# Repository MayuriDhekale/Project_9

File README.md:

# Project_9
<br>
<h2>A minimal RP2040 board designed in KiCad</h2>
<br>
I designed a small RP2040 board (like a Raspberry Pi Pico) in KiCad. I followed Raspberry Pi's official design guide to learn how a real board is made.

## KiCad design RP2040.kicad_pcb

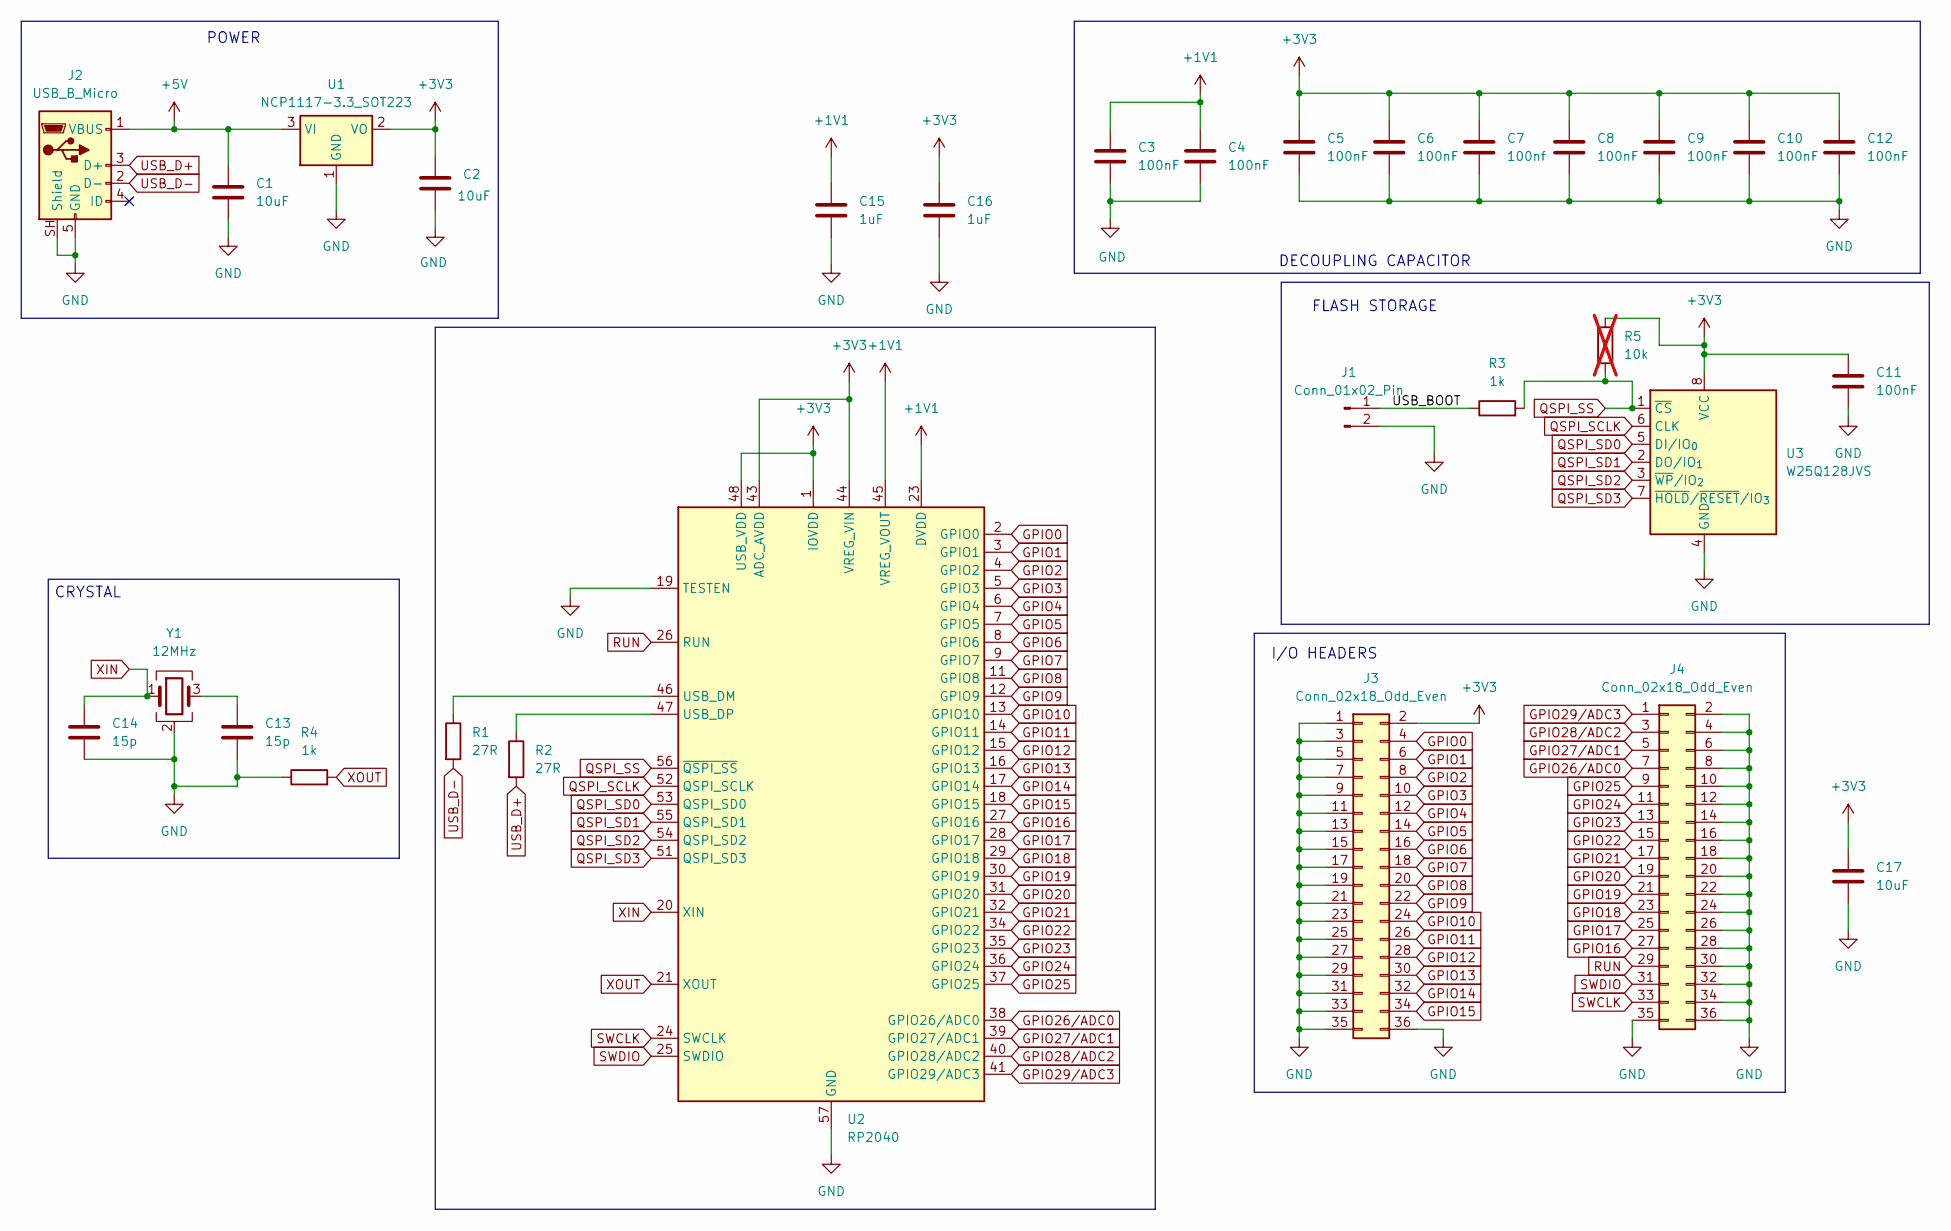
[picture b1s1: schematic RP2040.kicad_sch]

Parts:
C1, C2, C17: 10uF; C_0603_1608Metric
C3, C4, C5, C6, C8, C9, C10, C11, C12: 100nF; C_0603_1608Metric
C7: 100nf; C_0603_1608Metric
C13, C14: 15p; C_0603_1608Metric
C15, C16: 1uF; C_0603_1608Metric
J1: Conn_01x02_Pin; PinHeader_1x02_P2.54mm_Vertical
J2: USB_B_Micro; USB_Micro-B_Molex_47346-0001
J3, J4: Conn_02x18_Odd_Even; PinHeader_2x18_P2.54mm_Vertical
R1, R2: 27R; R_0603_1608Metric
R3, R4: 1k; R_0603_1608Metric
R5: 10k; R_0402_1005Metric; not fitted
U1: NCP1117-3.3_SOT223; SOT-223-3_TabPin2
U2: RP2040; QFN-56-1EP_7x7mm_P0.4mm_EP3.2x3.2mm
U3: W25Q128JVS; SOIC-8_5.3x5.3mm_P1.27mm
Y1: 12MHz; Crystal_SMD_3225-4Pin_3.2x2.5mm

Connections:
+1V1: C3.1, C4.1, C15.1, U2.23 (DVDD), U2.45 (VREG_VOUT), U2.50 (DVDD)
+3V3: C2.1, C5.1, C6.1, C7.1, C8.1, C9.1, C10.1, C11.1, C12.1, C16.1, C17.1, J3.2, R5.1, U1.2 (VO), U2.1 (IOVDD), U2.10 (IOVDD), U2.22 (IOVDD), U2.33 (IOVDD), U2.42 (IOVDD), U2.43 (ADC_AVDD), U2.44 (VREG_VIN), U2.48 (USB_VDD), U2.49 (IOVDD), U3.8 (VCC)
+5V: C1.1, J2.1 (VBUS), U1.3 (VI)
/USB_BOOT: J1.1, R3.1
GND: C1.2, C2.2, C3.2, C4.2, C5.2, C6.2, C7.2, C8.2, C9.2, C10.2, C11.2, C12.2, C13.2, C14.2, C15.2, C16.2, C17.2, J1.2, J2.5 (GND), J2.SH (Shield), J3.1, J3.3, J3.5, J3.7, J3.9, J3.11, J3.13, J3.15, J3.17, J3.19, J3.21, J3.23, J3.25, J3.27, J3.29, J3.31, J3.33, J3.35, J3.36, J4.2, J4.4, J4.6, J4.8, J4.10, J4.12, J4.14, J4.16, J4.18, J4.20, J4.22, J4.24, J4.26, J4.28, J4.30, J4.32, J4.34, J4.35, J4.36, R4.1, U1.1 (GND), U2.19 (TESTEN), U2.57 (GND), U3.4 (GND), Y1.2 (G), Y1.4 (G)
GPIO0: J3.4, U2.2 (GPIO0)
GPIO1: J3.6, U2.3 (GPIO1)
GPIO2: J3.8, U2.4 (GPIO2)
GPIO3: J3.10, U2.5 (GPIO3)
GPIO4: J3.12, U2.6 (GPIO4)
GPIO5: J3.14, U2.7 (GPIO5)
GPIO6: J3.16, U2.8 (GPIO6)
GPIO7: J3.18, U2.9 (GPIO7)
GPIO8: J3.20, U2.11 (GPIO8)
GPIO9: J3.22, U2.12 (GPIO9)
GPIO10: J3.24, U2.13 (GPIO10)
GPIO11: J3.26, U2.14 (GPIO11)
GPIO12: J3.28, U2.15 (GPIO12)
GPIO13: J3.30, U2.16 (GPIO13)
GPIO14: J3.32, U2.17 (GPIO14)
GPIO15: J3.34, U2.18 (GPIO15)
GPIO16: J4.27, U2.27 (GPIO16)
GPIO17: J4.25, U2.28 (GPIO17)
GPIO18: J4.23, U2.29 (GPIO18)
GPIO19: J4.21, U2.30 (GPIO19)
GPIO20: J4.19, U2.31 (GPIO20)
GPIO21: J4.17, U2.32 (GPIO21)
GPIO22: J4.15, U2.34 (GPIO22)
GPIO23: J4.13, U2.35 (GPIO23)
GPIO24: J4.11, U2.36 (GPIO24)
GPIO25: J4.9, U2.37 (GPIO25)
GPIO26/ADC0: J4.7, U2.38 (GPIO26/ADC0)
GPIO27/ADC1: J4.5, U2.39 (GPIO27/ADC1)
GPIO28/ADC2: J4.3, U2.40 (GPIO28/ADC2)
GPIO29/ADC3: J4.1, U2.41 (GPIO29/ADC3)
unnamed: C13.1, Y1.3
unnamed: R1.1, U2.46 (USB_DM)
unnamed: R2.1, U2.47 (USB_DP)
QSPI_SCLK: U2.52 (QSPI_SCLK), U3.6 (CLK)
QSPI_SD0: U2.53 (QSPI_SD0), U3.5 (DI/IO_{0})
QSPI_SD1: U2.55 (QSPI_SD1), U3.2 (DO/IO_{1})
QSPI_SD2: U2.54 (QSPI_SD2), U3.3 (~WP/IO_{2})
QSPI_SD3: U2.51 (QSPI_SD3), U3.7 (~HOLD/~RESET/IO_{3})
QSPI_SS: R3.2, R5.2, U2.56 (~QSPI_SS), U3.1 (~CS)
RUN: J4.29, U2.26 (RUN)
SWCLK: J4.33, U2.24 (SWCLK)
SWDIO: J4.31, U2.25 (SWDIO)
USB_D+: J2.3 (D+), R2.2
USB_D-: J2.2 (D-), R1.2
XIN: C14.1, U2.20 (XIN), Y1.1
XOUT: R4.2, U2.21 (XOUT)

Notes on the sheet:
POWER
I/O HEADERS
FLASH STORAGE
CRYSTAL
DECOUPLING CAPACITOR

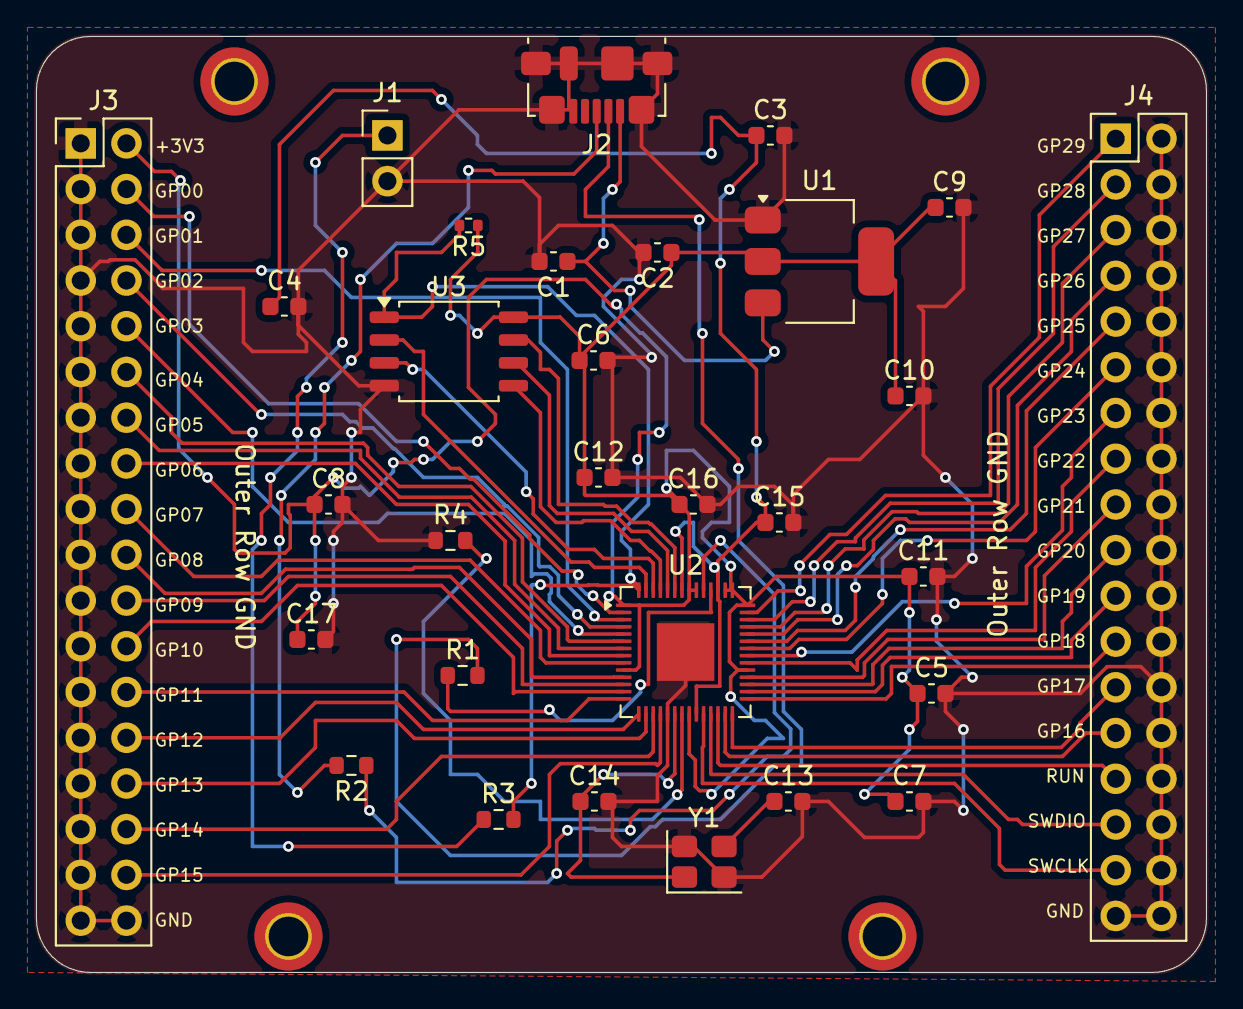
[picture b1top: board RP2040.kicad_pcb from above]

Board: 2 copper layers, 65.0 x 52.0 mm, 30 parts (0 on the bottom side), 51 nets.
